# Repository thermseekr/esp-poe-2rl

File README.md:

# eumesmo-poe-2rl
PoE powered ESP32 based board featuring two SPST NO relays. Ideal for access control, doors, isolated zones or for installing anywhere you need to click dry contacts near some equipment or appliance.

## VERSION HISTORY

V1.6 - 2026/07/02 - Added CPU health LED.

V1.5 - 2026/06/13 - Repository renamed from ESP-POE-2RL to eumesmo-poe-2rl to align the design with the **eumesmo** line of building automation products.

V1.4 - 2026/06/10 - Terminal blocks replaced for 3.5mm pitch. Deleted temperature sensor, board decreased 8mm in length. LAN8710A rotated for shorter traces. Pull-up resistor for MDIO adjusted from 2.2k to 1.5k as suggested in the datasheet. Bulk and decoupling capacitor sizes and types adjusted for better performance.

V1.3 - 2025/06/29 - Layers reordered and board fully rerouted for better signal integrity.

V1.2 - 2024/12/07 - Connectors adjusted for best fitting the case.

V1.1 - 2024/11/29 - Initial release.

## LICENSE

This project is licensed under the [Creative Commons BY-NC 4.0 License](https://creativecommons.org/licenses/by-nc/4.0/).
Commercial use is not permitted without prior written consent. See the [LICENSE.txt](LICENSE.txt) file for details.

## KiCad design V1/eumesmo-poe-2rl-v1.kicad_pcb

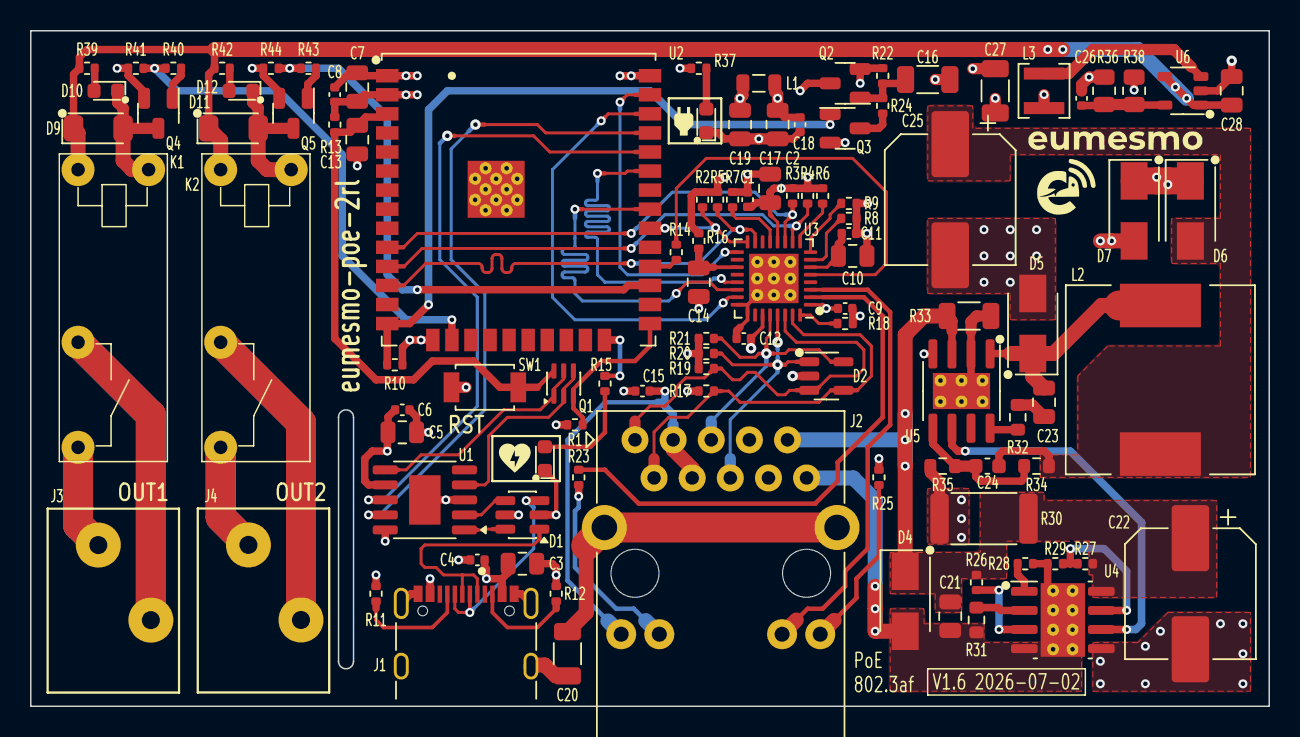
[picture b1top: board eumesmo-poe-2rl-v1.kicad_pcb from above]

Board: 4 copper layers, 82.5 x 45.0 mm, 105 parts (0 on the bottom side), 77 nets.

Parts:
C1, C4, C6, C8, C9, C12, C15, C18: 100nF/50V; C_0402_1005Metric
C2, C5, C7, C14, C17, C19, C28: 10uF/25V; C_0805_2012Metric
C3, C10, C13: 1uF/50V; C_0805_2012Metric
C11: 470pF/50V; C_0402_1005Metric
C16, C27: 22uF/10V; C_1206_3216Metric
C20: 1nF/2kV; C_1206_3216Metric
C21, C23: 100nF/100V; C_0805_2012Metric
C22: 22uF/100V; CP_Elec_8x10.5
C24: 12pF/50V; C_0603_1608Metric
C25: 470uF/16V; CP_Elec_8x10.5
C26: 22pF/50V; C_0402_1005Metric
D1: USBLC6-2SC6; SOT-23-6
D2: ESDS314DBV; SOT-23-5
D3: WHITE/0603; LED_0603_1608Metric
D4: SMAJ58A; D_SMA
D5: SS510; D_SMA
D6, D7: SS34; D_SMA
D8, D10, D12: WHITE; LED_0603_1608Metric
D9, D11: 1N4148; D_SOD-123
J1: USB_C_Receptacle_USB2.0; USB_C_Receptacle_GCT_USB4105-xx-A_16P_TopMnt_Horizontal
J2: RJ45 JACK; RJ45_HanRun_HY931147C
J3, J4: 250-202; TerminalBlock_Wago_250-202_1x02_P3.5mm_45Degree
K1, K2: G5NB-1A-E-DC5; Relay_SPST_Omron_G5NB-1A
L1: 2A/600R; L_0805_2012Metric
L2: 33uH/2,1A; L_12x12mm_H6mm
L3: 2,2uH/1,5A; L_3x3mm_H1.5mm
Q1: UMH3N; SOT-363_SC-70-6
Q2: WPM2015-3/TR; SOT-23
Q3: LMUN2211LT1G; SOT-23
Q4, Q5: MMBT2222A; SOT-23
R1, R10, R13, R16, R22, R29, R41, R44: 10k; R_0402_1005Metric
R2: 1.5k; R_0402_1005Metric
R3, R4, R5, R6, R7, R8, R9: 2.2k; R_0402_1005Metric
R11, R12: 5,1k; R_0402_1005Metric
R14: 33R; R_0402_1005Metric
R15, R37: 300R; R_0402_1005Metric
R17, R19, R20, R21: 49,9R; R_0402_1005Metric
R18: 12,1k; R_0402_1005Metric
R23, R25: 330R; R_0402_1005Metric
R24, R40, R43: 1k; R_0402_1005Metric
R26: 30,1k; R_0402_1005Metric
R27: 130k; R_0402_1005Metric
R28: 180k; R_0402_1005Metric
R30: 4,7k/1W; R_2512_6332Metric
R31: 4,42k/100mW; R_0603_1608Metric
R32: 5,1R/100mW; R_0603_1608Metric
R33: 30mR/250mW; R_1206_3216Metric
R34: 300k/100mW; R_0603_1608Metric
R35: 52,3k/100mW; R_0603_1608Metric
R36: 100k/0,125W; R_0805_2012Metric
R38: 22,1k/0,125W; R_0805_2012Metric
R39, R42: 680R; R_0402_1005Metric
SW1: RESET; SW_SPST_Xunpu_TS1088AR02016
U1: CH340K; SSOP-10-1EP_3.9x4.9mm_P1mm_EP2.1x3.3mm
U2: ESP32-WROOM-32UE-N16; ESP32-WROOM-32U
U3: LAN8710A; QFN-32-1EP_5x5mm_P0.5mm_EP3.3x3.3mm_ThermalVias
U4: TPS2376DDAR-H; SOIC-8-1EP_3.9x4.9mm_P1.27mm_EP2.95x4.9mm_Mask2.71x3.4mm_Th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
U5: TX4138; SOIC-8-1EP_3.9x4.9mm_P1.27mm_EP2.41x3.81mm_ThermalVias
U6: SY8089A1AAC; SOT-23-5_Shorter_Pins

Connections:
5VPOE: C24.1, C25.1, D6.2 (A), L2.2, R34.1
5VUSB: C3.1, C4.1, D1.5 (VBUS), D7.2 (A), J1.A4 (VBUS), J1.A9 (VBUS), J1.B4 (VBUS), J1.B9 (VBUS)
+3V3: C5.1, C6.1, C7.1, C8.1, C16.1, C26.1, C27.1, L3.2, Q2.2 (S), R1.1, R13.1, R22.1, R36.1, R37.1, U1.7 (VCC), U1.10 (V3), U2.2 (VDD)
+3V3A: C9.1, C12.1, C15.1, C19.1, J2.3 (CT), J2.4 (CT), J2.11 (LLED+), L1.2, R17.2, R19.2, R20.2, R21.2, U3.1 (VDD2A), U3.27 (VDD1A)
+3V3LAN: C1.1, C2.1, C17.1, C18.1, L1.1, Q2.3 (D), R2.1, R3.1, R4.1, R5.1, R6.1, R16.2, U3.12 (VDDIO)
+5V: C28.1, D6.1 (K), D7.1 (K), D9.1 (K), D11.1 (K), K1.1, K2.1, R39.1, R42.1, U6.1 (EN), U6.4 (IN)
/CPULED: D3.2 (A), R15.2
/CPUOK: R15.1, U2.24 (IO2)
/EMACCLK: R14.2, U3.5 (XTAL1/CLKIN)
/EMACMDC: U2.37 (IO23), U3.17 (MDC)
/EMACMDIO: R2.2, U2.30 (IO18), U3.16 (MDIO)
/EMACRX: R5.2, U2.12 (IO27), U3.15 (COL/CRS_DV/~MODE2)
/EMACRXCLK: R8.2, U3.7 (RXCLK/~PHYAD1)
/EMACRXD0: R3.2, U2.10 (IO25), U3.11 (RXD0/~MODE0)
/EMACRXD1: R4.2, U2.11 (IO26), U3.10 (RXD1/~MODE1)
/EMACRXD2: R6.2, U3.9 (RXD2/~RMIISEL)
/EMACRXD3: R9.2, U3.8 (RXD3/~PHYAD2)
/EMACRXD4: R7.2, U3.13 (RXER/RXD4/~PHYAD0)
/EMACTXD0: U2.31 (IO19), U3.22 (TXD0)
/EMACTXD1: U2.36 (IO22), U3.23 (TXD1)
/EMACTXEN: U2.33 (IO21), U3.21 (TXEN)
/ESPCLK: R14.1, U2.28 (IO17)
/ESPEN: C13.1, Q1.6 (C1), R13.2, SW1.2, U2.3 (EN)
/ESPPROG: Q1.3 (C2), R1.2, U2.25 (IO0)
/ETHLEDGA: J2.13 (RLED+), U3.3 (LED1/~REGOFF)
/ETHLEDGK: J2.14 (RLED-), R25.2
/ETHLEDY: R23.2, U3.2 (LED2/~INTSEL)
/ETHLEDYK: J2.12 (LLED-), R23.1
/ETHRXD+: D2.4 (I/03), J2.2 (RD+), R17.1, U3.31 (RXP)
/ETHRXD-: D2.3 (I/02), J2.1 (RD-), R19.1, U3.30 (RXN)
/ETHSH: C20.1, J2.15 (SHIELD)
/ETHTXD+: D2.1 (I/01), J2.6 (TD+), R20.1, U3.29 (TXP)
/ETHTXD-: D2.5 (I/04), J2.5 (TD-), R21.1, U3.28 (TXN)
/PHYNRST: C14.2, R16.1, U3.19 (~RST)
/PHYPWRBJT: Q3.3 (C), R24.2
/PHYPWRFET: C16.2, Q2.1 (G), R22.2, R24.1
/POWER/3V3LED: D8.2 (A), R37.2
/POWER/3V3REF: C26.2, R36.2, R38.1, U6.5 (FB)
/POWER/3V3SW: L3.1, U6.3 (LX)
/POWER/5VBS: C23.1, R32.1
/POWER/5VREF: C24.2, R34.2, R35.1, U5.5 (FB)
/POWER/5VSW: C23.2, D5.1 (K), L2.1, U5.1 (SW)
/POWER/BS: R32.2, U5.8 (BS)
/POWER/ILIM: R33.2, U5.2 (ILIM), U5.9 (ILIM)
/POWER/RCLASS: R31.1, U4.2 (CLASS)
/POWER/RDET: R26.2, U4.3 (DET)
/POWER/RILIM: R28.1, U4.1 (ILIM)
/POWER/VTAP: R27.2, R29.1, U4.7 (UVLO)
/RBIAS: R18.1, U3.32 (RBIAS)
/RELAY OUTPUTS/OUT1BJT: Q4.1 (B), R40.1
/RELAY OUTPUTS/OUT1CMD: D9.2 (A), D10.1 (K), K1.4, Q4.3 (C)
/RELAY OUTPUTS/OUT1LD: J3.1, K1.3
/RELAY OUTPUTS/OUT1LN: J3.2, K1.2
/RELAY OUTPUTS/OUT1ON: D10.2 (A), R39.2
/RELAY OUTPUTS/OUT2BJT: Q5.1 (B), R43.1
/RELAY OUTPUTS/OUT2CMD: D11.2 (A), D12.1 (K), K2.4, Q5.3 (C)
/RELAY OUTPUTS/OUT2LD: J4.1, K2.3
/RELAY OUTPUTS/OUT2LN: J4.2, K2.2
/RELAY OUTPUTS/OUT2ON: D12.2 (A), R42.2
/UARTNDTR: Q1.2 (B1), Q1.4 (E2), U1.4 (~DTR)
/UARTNRTS: Q1.1 (E1), Q1.5 (B2), U1.6 (~RTS)
/UARTRXD: U1.9 (RXD), U2.35 (TXD0/IO1)
/UARTTXD: U1.8 (TXD), U2.34 (RXD0/IO3)
/USBCC1: J1.A5 (CC1), R11.1
/USBCC2: J1.B5 (CC2), R12.1
/USBCD+: D1.1 (I/O1), J1.A6 (D+), J1.B6 (D+)
/USBCD-: D1.3 (I/O2), J1.A7 (D-), J1.B7 (D-)
/USBD+: D1.6 (I/O1), U1.1 (UD+)
/USBD-: D1.4 (I/O2), U1.2 (UD-)
/VDDCR: C10.1, C11.1, U3.6 (VDDCR)
GND: C1.2, C2.2, C3.2, C4.2, C5.2, C6.2, C7.2, C8.2, C9.2, C10.2, C11.2, C12.2, C13.2, C14.1, C15.2, C17.2, C18.2, C19.2, C20.2, C22.2, C25.2, C27.2, C28.2, D1.2 (GND), D2.2 (GND), D3.1 (K), D5.2 (A), D8.1 (K), J1.A1 (GND), J1.A12 (GND), J1.B1 (GND), J1.B12 (GND), J1.S1 (SHIELD), Q3.2 (E), Q4.2 (E), Q5.2 (E), R7.1, R8.1, R9.1, R10.1, R11.2, R12.2, R18.2, R25.1, R30.2, R35.2, R38.2, R41.2, R44.2, SW1.1, U1.3 (GND), U1.11 (GND), U2.1 (GND), U2.15 (GND), U2.38 (GND), U2.39 (GND), U3.24 (TXD2), U3.25 (TXD3), U3.33 (VSS), U4.5 (RTN), U5.4 (GND), U6.2 (GND)
OUT1: R40.2, R41.1, U2.16 (IO13)
OUT2: R43.2, R44.1, U2.27 (IO16)
PG: U4.6 (PG), U5.6 (EN)
PHYPWR: Q3.1 (B), R10.2, U2.14 (IO12)
POE+: C21.1, C22.1, D4.1 (K), J2.9 (V+), R26.1, R27.1, R30.1, R33.1, U4.8 (VDD), U5.3 (VIN)
POE-: C21.2, D4.2 (A), J2.10 (V-), R28.2, R29.2, R31.2, U4.4 (VSS), U4.9 (PPAD)

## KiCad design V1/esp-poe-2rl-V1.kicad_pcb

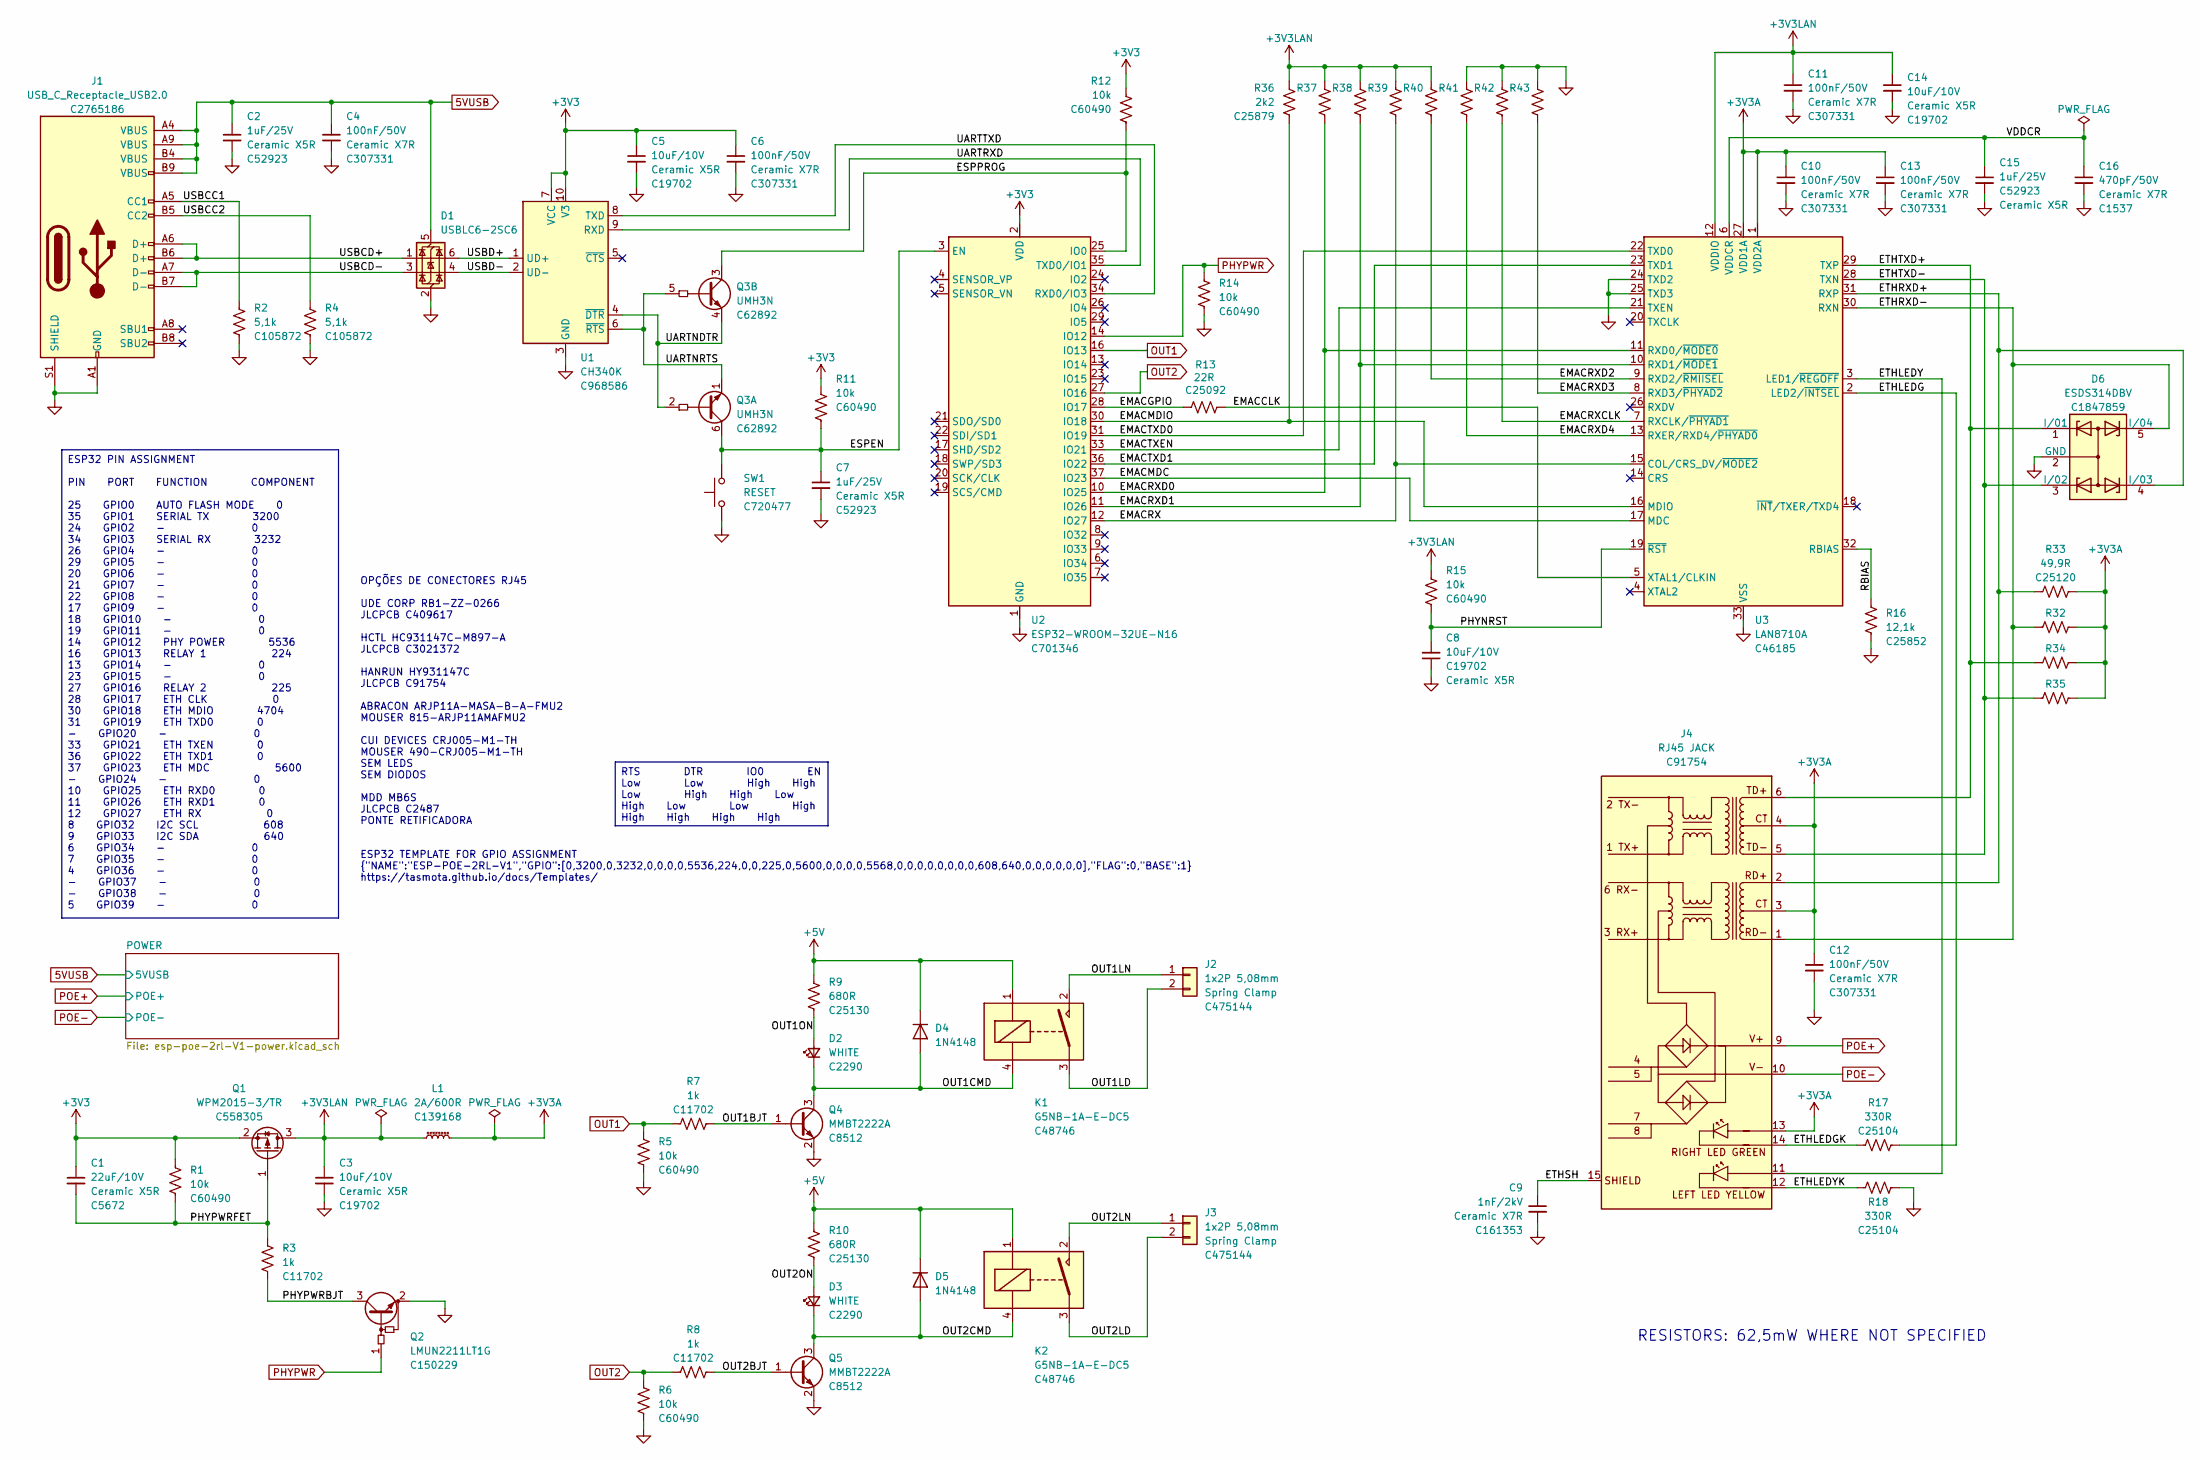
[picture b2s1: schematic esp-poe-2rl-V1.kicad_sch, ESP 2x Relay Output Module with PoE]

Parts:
C1: 22uF/10V; C_1206_3216Metric; Mfr PN CL31A226KPHNNNE; JLCPCB BOM 1
C2, C7, C15: 1uF/25V; C_0402_1005Metric; Mfr PN CL05A105KA5NQNC; JLCPCB BOM 1
C3, C8, C14: 10uF/10V; C_0603_1608Metric; Mfr PN CL10A106KP8NNNC; JLCPCB BOM 1
C4, C6, C10, C11, C12, C13: 100nF/50V; C_0402_1005Metric; Mfr PN CL05B104KB54PNC; JLCPCB BOM 1
C5: 10uF/10V; C_0603_1608Metric; Mfr PN CL10A106KP8NNNC; LCSC Part # C19702
C9: 1nF/2kV; C_1206_3216Metric; Mfr PN GR431BR7LA102KW66L; JLCPCB BOM 1
C16: 470pF/50V; C_0402_1005Metric; Mfr PN 0402B471K500NT; JLCPCB BOM 1
D1: USBLC6-2SC6; SOT-23-6; Mfr PN USBLC6-2SC6; JLCPCB BOM 1
D2, D3: WHITE; LED_0603_1608Metric; Mfr PN KT-0603W; LCSC Part # C2290
D4, D5: 1N4148; D_SOD-123; Mfr PN 1N4148W; JLCPCB BOM 1
D6: ESDS314DBV; SOT-23-5; Mfr PN ESDS314DBVR; JLCPCB BOM 1
J1: USB_C_Receptacle_USB2.0; USB_C_Receptacle_GCT_USB4105-xx-A_16P_TopMnt_Horizontal; Mfr PN TYPE-C 16PIN 2MD(073); JLCPCB BOM 1
J2, J3: 1x2P 5,08mm; TerminalBlock_Dibo_DB142R-5.08-2P_1x02_P5.08mm_Horizontal; Mfr PN KF142R-5.08-2P; JLCPCB BOM 1
J4: RJ45 JACK; RJ45_HanRun_HY931147C; Mfr PN HY931147C; JLCPCB BOM 1
K1, K2: G5NB-1A-E-DC5; Relay_SPST_Omron_G5NB-1A; Mfr PN G5NB-1A-E-DC5; JLCPCB BOM 1
L1: 2A/600R; L_0805_2012Metric; Mfr PN CBM201209U601T; JLCPCB BOM 1
Q1: WPM2015-3/TR; SOT-23; Mfr PN WPM2015-3/TR; JLCPCB BOM 1
Q2: LMUN2211LT1G; SOT-23; Mfr PN MMUN2211LT3G; LCSC Part # C150229
Q3: UMH3N; SOT-363_SC-70-6; Mfr PN UMH3N; JLCPCB BOM 1
Q4, Q5: MMBT2222A; SOT-23; Mfr PN MMBT2222A; JLCPCB BOM 1
R1, R5, R6, R11, R12, R14, R15: 10k; R_0402_1005Metric; Mfr PN RC0402FR-0710KL; LCSC Part # C60490
R2, R4: 5,1k; R_0402_1005Metric; Mfr PN RC0402FR-075K1L; JLCPCB BOM 1
R3, R7, R8: 1k; R_0402_1005Metric; Mfr PN 0402WGF1001TCE; LCSC Part # C11702
R9, R10: 680R; R_0402_1005Metric; Mfr PN 0402WGF6800TCE; LCSC Part # C25130
R13: 22R; R_0402_1005Metric; Mfr PN 0402WGF220JTCE; JLCPCB BOM 1
R16: 12,1k; R_0402_1005Metric; Mfr PN 0402WGF1212TCE; JLCPCB BOM 1
R17, R18: 330R; R_0402_1005Metric; Mfr PN 0402WGF3300TCE; LCSC Part # C25104
R32, R33, R34, R35: 49,9R; R_0402_1005Metric; Mfr PN 0402WGF499JTCE; JLCPCB BOM 1
R36, R37, R38, R39, R40, R41, R42, R43: 2k2; R_0402_1005Metric; Mfr PN 0402WGF2201TCE; LCSC Part # C25879
SW1: RESET; SW_SPST_Xunpu_TS1088AR02016; Mfr PN TS-1088-AR02016; JLCPCB BOM 1
U1: CH340K; SSOP-10-1EP_3.9x4.9mm_P1mm_EP2.1x3.3mm; Mfr PN CH340K; JLCPCB BOM 1
U2: ESP32-WROOM-32UE-N16; ESP32-WROOM-32U; Mfr PN ESP32-WROOM-32UE-N16; JLCPCB BOM 1
U3: LAN8710A; QFN-32-1EP_5x5mm_P0.5mm_EP3.3x3.3mm_ThermalVias; Mfr PN LAN8710A-EZC-TR; JLCPCB BOM 1

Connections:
5VUSB: C2.1, C4.1, D1.5 (VBUS), J1.A4 (VBUS), J1.A9 (VBUS), J1.B4 (VBUS), J1.B9 (VBUS); also elsewhere on the board
+3V3: C1.1, C5.1, C6.1, Q1.2 (S), R1.1, R11.1, R12.1, U1.7 (VCC), U1.10 (V3), U2.2 (VDD); also elsewhere on the board
+3V3A: C10.1, C12.1, C13.1, J4.3 (CT), J4.4 (CT), J4.13 (RLED+), L1.2, R32.2, R33.2, R34.2, R35.2, U3.1 (VDD2A), U3.27 (VDD1A)
+3V3LAN: C3.1, C11.1, C14.1, L1.1, Q1.3 (D), R15.2, R36.1, R37.1, R38.1, R39.1, R40.1, U3.12 (VDDIO)
+5V: D4.1 (K), D5.1 (K), K1.1, K2.1, R9.1, R10.1; also elsewhere on the board
/EMACCLK: R13.2, U3.5 (XTAL1/CLKIN)
/EMACGPIO: R13.1, U2.28 (IO17)
/EMACMDC: U2.37 (IO23), U3.17 (MDC)
/EMACMDIO: R36.2, U2.30 (IO18), U3.16 (MDIO)
/EMACRX: R39.2, U2.12 (IO27), U3.15 (COL/CRS_DV/~MODE2)
/EMACRXCLK: R42.2, U3.7 (RXCLK/~PHYAD1)
/EMACRXD0: R37.2, U2.10 (IO25), U3.11 (RXD0/~MODE0)
/EMACRXD1: R38.2, U2.11 (IO26), U3.10 (RXD1/~MODE1)
/EMACRXD2: R40.2, U3.9 (RXD2/~RMIISEL)
/EMACRXD3: R43.2, U3.8 (RXD3/~PHYAD2)
/EMACRXD4: R41.2, U3.13 (RXER/RXD4/~PHYAD0)
/EMACTXD0: U2.31 (IO19), U3.22 (TXD0)
/EMACTXD1: U2.36 (IO22), U3.23 (TXD1)
/EMACTXEN: U2.33 (IO21), U3.21 (TXEN)
/ESPEN: C7.1, Q3.6 (C1), R11.2, SW1.2, U2.3 (EN)
/ESPPROG: Q3.3 (C2), R12.2, U2.25 (IO0)
/ETHLEDG: R17.2, U3.2 (LED2/~INTSEL)
/ETHLEDGK: J4.14 (RLED-), R17.1
/ETHLEDY: J4.11 (LLED+), U3.3 (LED1/~REGOFF)
/ETHLEDYK: J4.12 (LLED-), R18.1
/ETHRXD+: D6.4 (I/03), J4.2 (RD+), R33.1, U3.31 (RXP)
/ETHRXD-: D6.5 (I/04), J4.1 (RD-), R32.1, U3.30 (RXN)
/ETHSH: C9.1, J4.15 (SHIELD)
/ETHTXD+: D6.1 (I/01), J4.6 (TD+), R34.1, U3.29 (TXP)
/ETHTXD-: D6.3 (I/02), J4.5 (TD-), R35.1, U3.28 (TXN)
/OUT1BJT: Q4.1 (B), R7.1
/OUT1CMD: D2.1 (K), D4.2 (A), K1.4, Q4.3 (C)
/OUT1LD: J2.2, K1.3
/OUT1LN: J2.1, K1.2
/OUT1ON: D2.2 (A), R9.2
/OUT2BJT: Q5.1 (B), R8.1
/OUT2CMD: D3.1 (K), D5.2 (A), K2.4, Q5.3 (C)
/OUT2LD: J3.2, K2.3
/OUT2LN: J3.1, K2.2
/OUT2ON: D3.2 (A), R10.2
/PHYNRST: C8.2, R15.1, U3.19 (~RST)
/PHYPWRBJT: Q2.3 (C), R3.2
/PHYPWRFET: C1.2, Q1.1 (G), R1.2, R3.1
/RBIAS: R16.1, U3.32 (RBIAS)
/UARTNDTR: Q3.2 (B1), Q3.4 (E2), U1.4 (~DTR)
/UARTNRTS: Q3.1 (E1), Q3.5 (B2), U1.6 (~RTS)
/UARTRXD: U1.9 (RXD), U2.35 (TXD0/IO1)
/UARTTXD: U1.8 (TXD), U2.34 (RXD0/IO3)
/USBCC1: J1.A5 (CC1), R2.1
/USBCC2: J1.B5 (CC2), R4.1
/USBCD+: D1.1 (I/O1), J1.A6 (D+), J1.B6 (D+)
/USBCD-: D1.3 (I/O2), J1.A7 (D-), J1.B7 (D-)
/USBD+: D1.6 (I/O1), U1.1 (UD+)
/USBD-: D1.4 (I/O2), U1.2 (UD-)
/VDDCR: C15.1, C16.1, U3.6 (VDDCR)
GND: C2.2, C3.2, C4.2, C5.2, C6.2, C7.2, C8.1, C9.2, C10.2, C11.2, C12.2, C13.2, C14.2, C15.2, C16.2, D1.2 (GND), D6.2 (GND), J1.A1 (GND), J1.A12 (GND), J1.B1 (GND), J1.B12 (GND), J1.S1 (SHIELD), Q2.2 (E), Q4.2 (E), Q5.2 (E), R2.2, R4.2, R5.2, R6.2, R14.1, R16.2, R18.2, R41.1, R42.1, R43.1, SW1.1, U1.3 (GND), U1.11 (GND), U2.1 (GND), U2.15 (GND), U2.38 (GND), U2.39 (GND), U3.24 (TXD2), U3.25 (TXD3), U3.33 (VSS); also elsewhere on the board
OUT1: R5.1, R7.2, U2.16 (IO13)
OUT2: R6.1, R8.2, U2.27 (IO16)
PHYPWR: Q2.1 (B), R14.2, U2.14 (IO12)
POE+: J4.9 (V+); also elsewhere on the board
POE-: J4.10 (V-); also elsewhere on the board

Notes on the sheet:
OPÇÕES DE CONECTORES RJ45 UDE CORP RB1-ZZ-0266 JLCPCB C409617 HCTL HC931147C-M897-A JLCPCB C3021372 HANRUN HY931147C JLCPCB C91754 ABRACON ARJP11A-MASA-B-A-FMU2 MOUSER 815-ARJP11AMAFMU2 CUI DEVICES CRJ005-M1-TH MOUSER 490-CRJ005-M1-TH SEM LEDS SEM DIODOS MDD MB6S JLCPCB C2487 PONTE RETIFICADORA
ESP32 TEMPLATE FOR GPIO ASSIGNMENT {"NAME":"ESP-POE-2RL-V1","GPIO":[0,3200,0,3232,0,0,0,0,5536,224,0,0,225,0,5600,0,0,0,0,5568,0,0,0,0,0,0,0,0,608,640,0,0,0,0,0,0],"FLAG":0,"BASE":1} https://tasmota.github.io/docs/Templates/
RESISTORS: 62,5mW WHERE NOT SPECIFIED
ESP32 PIN ASSIGNMENT PIN PORT FUNCTION COMPONENT 25 GPIO0 AUTO FLASH MODE 0 35 GPIO1 SERIAL TX 3200 24 GPIO2 - 0 34 GPIO3 SERIAL RX 3232 26 GPIO4 - 0 29 GPIO5 - 0 20 GPIO6 - 0 21 GPIO7 - 0 22 GPIO8 - 0 17 GPIO9 - 0 18 GPIO10 - 0 19 GPIO11 - 0 14 GPIO12 PHY POWER 5536 16 GPIO13 RELAY 1 224 13 GPIO14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
RTS DTR IO0 EN Low Low High High Low High High Low High Low Low High High High High High

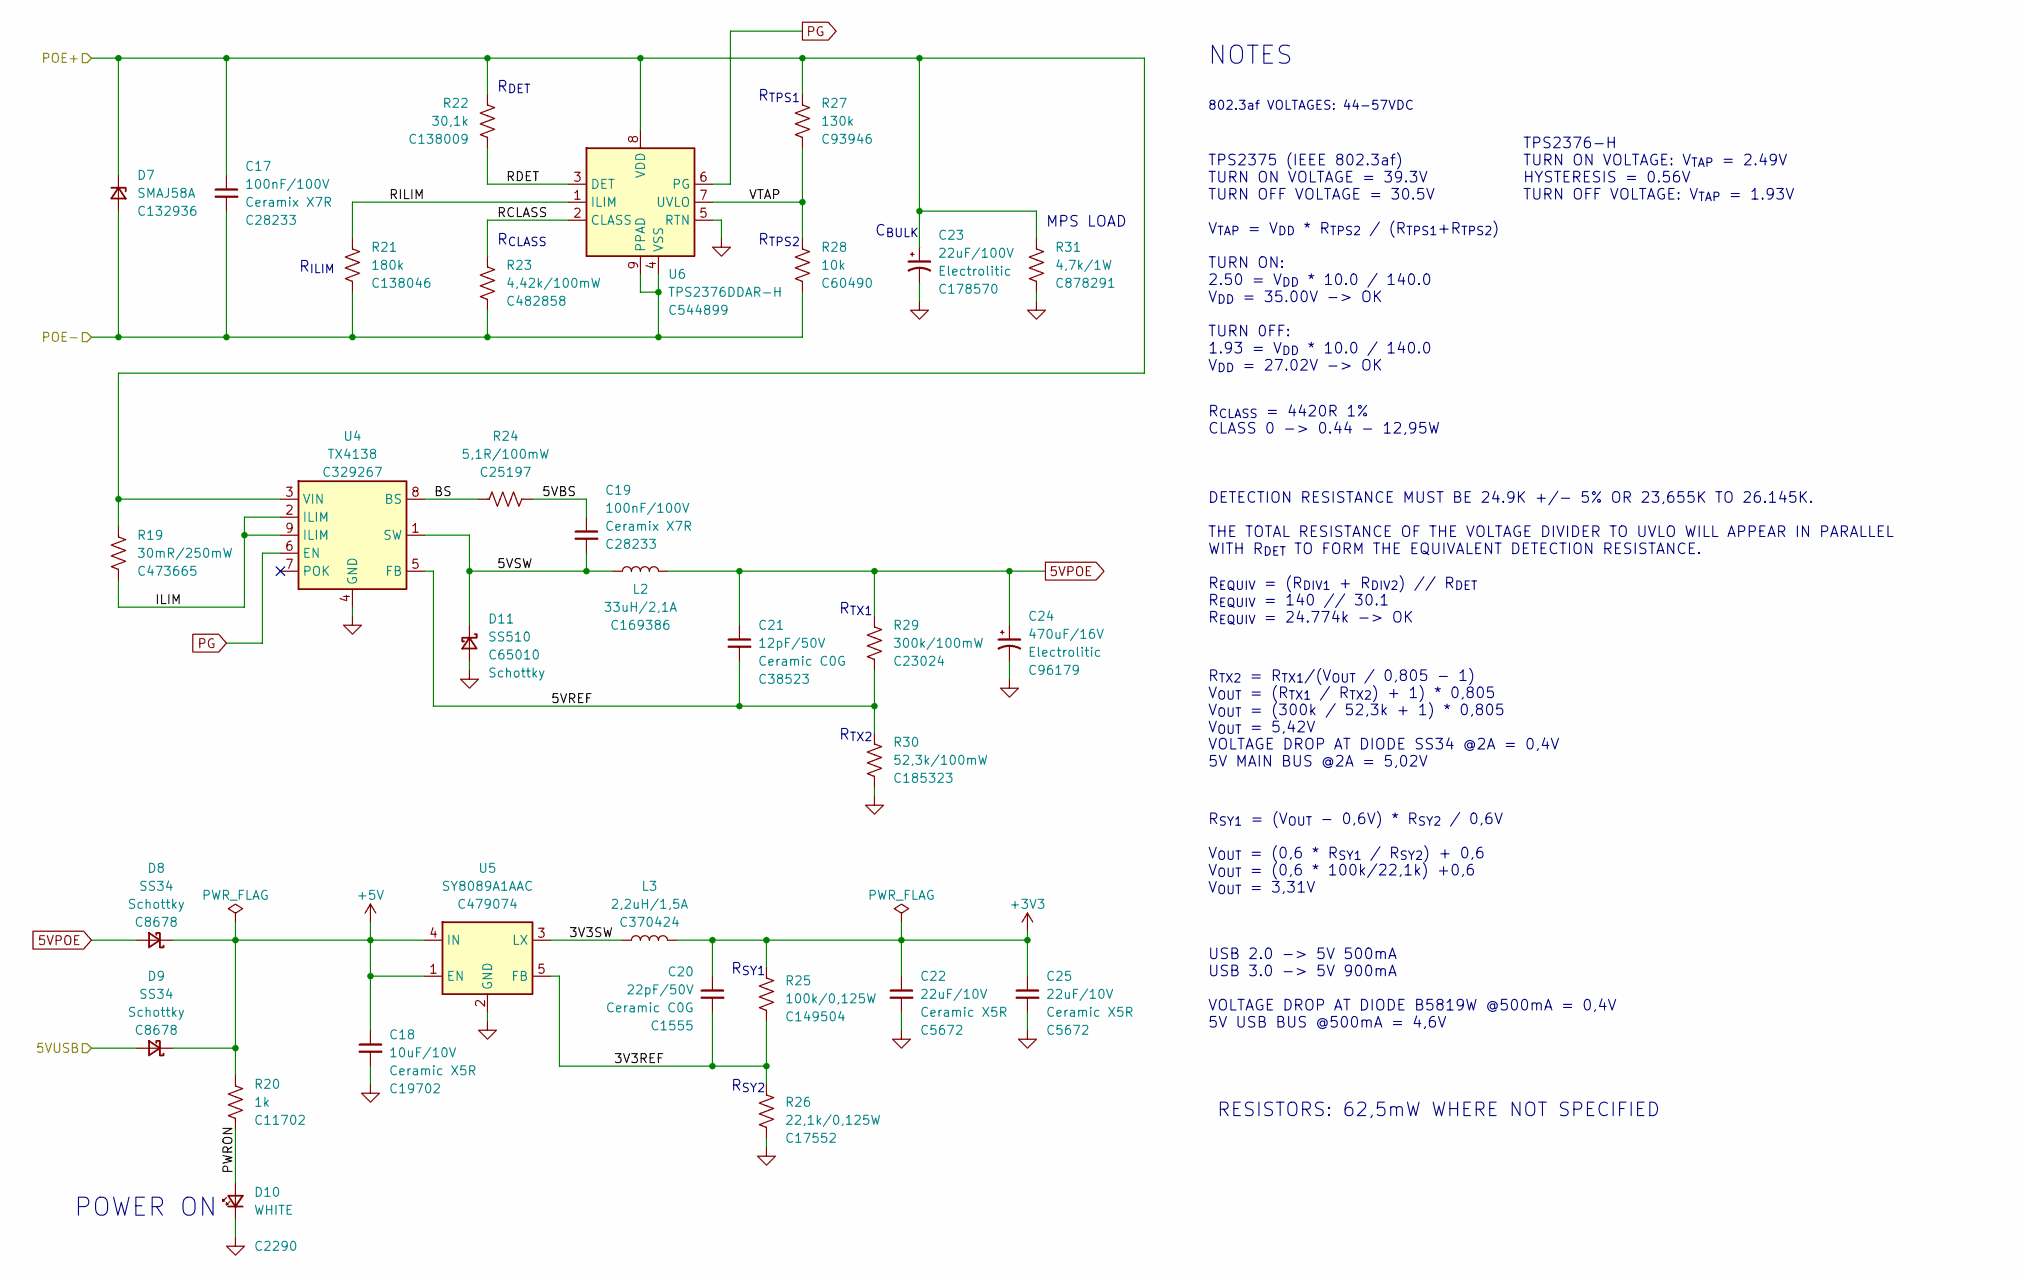
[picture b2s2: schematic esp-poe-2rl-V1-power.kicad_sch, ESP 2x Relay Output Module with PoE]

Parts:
C17: 100nF/100V; C_0805_2012Metric; Mfr PN CL21B104KCFNNNE; JLCPCB BOM 1
C18: 10uF/10V; C_0603_1608Metric; Mfr PN CL10A106KP8NNNC; JLCPCB BOM 1
C19: 100nF/100V; C_0805_2012Metric; Mfr PN CL21B104KCFNNNE; LCSC Part # C28233
C20: 22pF/50V; C_0402_1005Metric; Mfr PN 0402CG220J500NT; JLCPCB BOM 1
C21: 12pF/50V; C_0603_1608Metric; Mfr PN CL10C120JB8NNNC; JLCPCB BOM 1
C22, C25: 22uF/10V; C_1206_3216Metric; Mfr PN CL31A226KPHNNNE; JLCPCB BOM 1
C23: 22uF/100V; CP_Elec_8x10.5; Mfr PN EEEFK2A220P; LCSC Part # C178570
C24: 470uF/16V; CP_Elec_8x10.5; Mfr PN CS1C471M-CRF10; JLCPCB BOM 1
D7: SMAJ58A; D_SMA; Mfr PN SMAJ58A-TR; JLCPCB BOM 1
D8, D9: SS34; D_SMA; Mfr PN SS34; JLCPCB BOM 1
D10: WHITE; LED_0603_1608Metric; Mfr PN KT-0603W; LCSC Part # C2290
D11: SS510; D_SMA; Mfr PN SS510; JLCPCB BOM 1
L2: 33uH/2,1A; L_12x12mm_h6mm; Mfr PN SWRB1205S-330MT; JLCPCB BOM 1
L3: 2,2uH/1,5A; L_3x3mm_h1.5mm; Mfr PN SPH3015H2R2MT; JLCPCB BOM 1
R19: 30mR/250mW; R_1206_3216Metric; Mfr PN 1206W3F300MT5E; LCSC Part # C473665
R20: 1k; R_0402_1005Metric; Mfr PN 0402WGF1001TCE; LCSC Part # C11702
R21: 180k; R_0402_1005Metric; Mfr PN RC0402FR-07180KL; JLCPCB BOM 1
R22: 30,1k; R_0402_1005Metric; Mfr PN RC0402FR-0730K1L; JLCPCB BOM 1
R23: 4,42k/100mW; R_0603_1608Metric; Mfr PN RC0603FR-074K42L; JLCPCB BOM 1
R24: 5,1R/100mW; R_0603_1608Metric; Mfr PN 0603WAF510KT5E; LCSC Part # C25197
R25: 100k/0,125W; R_0805_2012Metric; Mfr PN 0805W8F1003T5E; JLCPCB BOM 1
R26: 22,1k/0,125W; R_0805_2012Metric; Mfr PN 0805W8F2212T5E; JLCPCB BOM 1
R27: 130k; R_0402_1005Metric; Mfr PN RC0402FR-07130KL; JLCPCB BOM 1
R28: 10k; R_0402_1005Metric; Mfr PN RC0402FR-0710KL; JLCPCB BOM 1
R29: 300k/100mW; R_0603_1608Metric; Mfr PN 0603WAF3003T5E; JLCPCB BOM 1
R30: 52,3k/100mW; R_0603_1608Metric; Mfr PN RC0603FR-0752K3L; JLCPCB BOM 1
R31: 4,7k/1W; R_2512_6332Metric; Mfr PN RC2512JK-074K7L; JLCPCB BOM 1
U4: TX4138; SOIC-8-1EP_3.9x4.9mm_P1.27mm_EP2.41x3.81mm_ThermalVias; Mfr PN TX4138; JLCPCB BOM 1
U5: SY8089A1AAC; SOT-23-5_Shorter_Pins; Mfr PN SY8089A1AAC; JLCPCB BOM 1
U6: TPS2376DDAR-H; SOIC-8-1EP_3.9x4.9mm_P1.27mm_EP2.95x4.9mm_Mask2.71x3.4mm_Th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; Mfr PN TPS2376DDAR-H; JLCPCB BOM 1

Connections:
5VPOE: C21.1, C24.1, D8.2 (A), L2.2, R29.1
5VUSB: D9.2 (A); also elsewhere on the board
+3V3: C20.1, C22.1, C25.1, L3.2, R25.1; also elsewhere on the board
+5V: C18.1, D8.1 (K), D9.1 (K), R20.1, U5.1 (EN), U5.4 (IN); also elsewhere on the board
/POWER/3V3REF: C20.2, R25.2, R26.1, U5.5 (FB)
/POWER/3V3SW: L3.1, U5.3 (LX)
/POWER/5VBS: C19.1, R24.1
/POWER/5VREF: C21.2, R29.2, R30.1, U4.5 (FB)
/POWER/5VSW: C19.2, D11.1 (K), L2.1, U4.1 (SW)
/POWER/BS: R24.2, U4.8 (BS)
/POWER/ILIM: R19.2, U4.2 (ILIM), U4.9 (ILIM)
/POWER/PWRON: D10.2 (A), R20.2
/POWER/RCLASS: R23.1, U6.2 (CLASS)
/POWER/RDET: R22.2, U6.3 (DET)
/POWER/RILIM: R21.1, U6.1 (ILIM)
/POWER/VTAP: R27.2, R28.1, U6.7 (UVLO)
GND: C18.2, C22.2, C23.2, C24.2, C25.2, D10.1 (K), D11.2 (A), R26.2, R30.2, R31.2, U4.4 (GND), U5.2 (GND), U6.5 (RTN); also elsewhere on the board
PG: U4.6 (EN), U6.6 (PG)
POE+: C17.1, C23.1, D7.1 (K), R19.1, R22.1, R27.1, R31.1, U4.3 (VIN), U6.8 (VDD); also elsewhere on the board
POE-: C17.2, D7.2 (A), R21.2, R23.2, R28.2, U6.4 (VSS), U6.9 (PPAD); also elsewhere on the board

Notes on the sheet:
R_{TPS1}
R_{TX2}
DETECTION RESISTANCE MUST BE 24.9K +/- 5% OR 23,655K TO 26.145K. THE TOTAL RESISTANCE OF THE VOLTAGE DIVIDER TO UVLO WILL APPEAR IN PARALLEL WITH R_{DET} TO FORM THE EQUIVALENT DETECTION RESISTANCE. R_{EQUIV} = (R_{DIV1} + R_{DIV2}) // R_{DET} R_{EQUIV} = 140 // 30.1 R_{EQUIV} = 24.774k -> OK
R_{SY2}
RESISTORS: 62,5mW WHERE NOT SPECIFIED
POWER ON
R_{CLASS} = 4420R 1% CLASS 0 -> 0.44 - 12,95W
R_{SY1}
R_{CLASS}
R_{TX2} = R_{TX1}/(V_{OUT} / 0,805 - 1) V_{OUT} = (R_{TX1} / R_{TX2}) + 1) * 0,805 V_{OUT} = (300k / 52,3k + 1) * 0,805 V_{OUT} = 5,42V VOLTAGE DROP AT DIODE SS34 @2A = 0,4V 5V MAIN BUS @2A = 5,02V
C_{BULK}
R_{ILIM}
USB 2.0 -> 5V 500mA USB 3.0 -> 5V 900mA VOLTAGE DROP AT DIODE B5819W @500mA = 0,4V 5V USB BUS @500mA = 4,6V
TPS2375 (IEEE 802.3af) TURN ON VOLTAGE = 39.3V TURN OFF VOLTAGE = 30.5V
TPS2376-H TURN ON VOLTAGE: V_{TAP} = 2.49V HYSTERESIS = 0.56V TURN OFF VOLTAGE: V_{TAP} = 1.93V
R_{SY1} = (V_{OUT} - 0,6V) * R_{SY2} / 0,6V V_{OUT} = (0,6 * R_{SY1} / R_{SY2}) + 0,6 V_{OUT} = (0,6 * 100k/22,1k) +0,6 V_{OUT} = 3,31V
R_{TPS2}
R_{TX1}
NOTES
MPS LOAD
R_{DET}
802.3af VOLTAGES: 44-57VDC
V_{TAP} = V_{DD} * R_{TPS2} / (R_{TPS1}+R_{TPS2}) TURN ON: 2.50 = V_{DD} * 10.0 / 140.0 V_{DD} = 35.00V -> OK TURN 0FF: 1.93 = V_{DD} * 10.0 / 140.0 V_{DD} = 27.02V -> OK

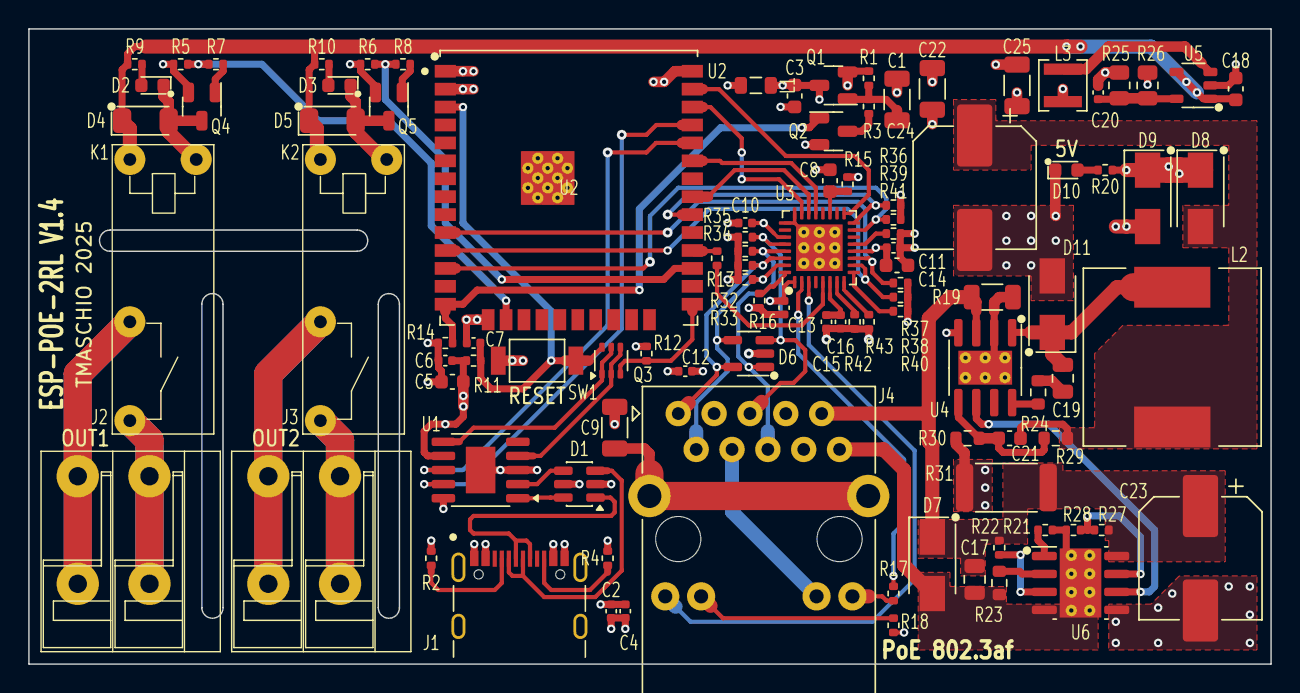
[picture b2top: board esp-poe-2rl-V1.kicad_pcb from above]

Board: 4 copper layers, 88.0 x 45.0 mm, 100 parts (0 on the bottom side), 75 nets.

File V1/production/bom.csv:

Designator,Footprint,Quantity,Value,LCSC Part #
"C1, C22, C25",1206,3,22uF/10V,C5672
"C10, C11, C12, C13, C4, C6",0402,6,100nF/50V,C307331
"C14, C18, C3, C5, C8",0603,5,10uF/10V,C19702
"C15, C2, C7",0402,3,1uF/25V,C52923
C16,0402,1,470pF/50V,C1537
"C17, C19",0805,2,100nF/100V,C28233
C20,0402,1,22pF/50V,C1555
C21,0603,1,12pF/50V,C38523
C23,CP_Elec_8x10.5,1,22uF/100V,C178570
C24,CP_Elec_8x10.5,1,470uF/16V,C96179
C9,1206,1,1nF/2kV,C161353
D1,SOT-23-6,1,USBLC6-2SC6,C7519
"D10, D2, D3",0603,3,WHITE,C2290
D11,D_SMA,1,SS510,C65010
"D4, D5",D_SOD-123,2,1N4148,C81598
D6,SOT-23-5,1,ESDS314DBV,C1847859
D7,D_SMA,1,SMAJ58A,C132936
"D8, D9",D_SMA,2,SS34,C8678
J1,USB_C_Receptacle_GCT_USB4105-xx-A_16P_TopMnt_Horizontal,1,USB_C_Receptacle_USB2.0,C2765186
"J2, J3",TerminalBlock_Dibo_DB142R-5.08-2P_1x02_P5.08mm_Horizontal,2,"1x2P 5,08mm",C475144
J4,RJ45_HanRun_HY931147C,1,RJ45 JACK,C91754
"K1, K2",Relay_SPST_Omron_G5NB-1A,2,G5NB-1A-E-DC5,C48746
L1,0805,1,2A/600R,C139168
L2,L_12x12mm_h6mm,1,"33uH/2,1A",C169386
L3,L_3x3mm_h1.5mm,1,"2,2uH/1,5A",C370424
Q1,SOT-23,1,WPM2015-3/TR,C558305
Q2,SOT-23,1,LMUN2211LT1G,C150229
Q3,SOT-363_SC-70-6,1,UMH3N,C62892
"Q4, Q5",SOT-23,2,MMBT2222A,C8512
"R1, R11, R12, R14, R15, R28, R5, R6",0402,8,10k,C60490
"R10, R9",0402,2,680R,C25130
R13,0402,1,22R,C25092
R16,0402,1,"12,1k",C25852
"R17, R18",0402,2,330R,C25104
R19,1206,1,30mR/250mW,C473665
"R2, R4",0402,2,"5,1k",C105872
"R20, R3, R7, R8",0402,4,1k,C11702
R21,0402,1,180k,C138046
R22,0402,1,"30,1k",C138009
R23,0603,1,"4,42k/100mW",C482858
R24,0603,1,"5,1R/100mW",C25197
R25,0805,1,"100k/0,125W",C149504
R26,0805,1,"22,1k/0,125W",C17552
R27,0402,1,130k,C93946
R29,0603,1,300k/100mW,C23024
R30,0603,1,"52,3k/100mW",C185323
R31,2512,1,"4,7k/1W",C878291
"R32, R33, R34, R35",0402,4,"49,9R",C25120
"R36, R37, R38, R39, R40, R41, R42, R43",0402,8,2k2,C25879
SW1,SW_SPST_Xunpu_TS1088AR02016,1,RESET,C720477
U1,SSOP-10-1EP_3.9x4.9mm_P1mm_EP2.1x3.3mm,1,CH340K,C968586
U2,ESP32-WROOM-32U,1,ESP32-WROOM-32UE-N16,C701346
U3,QFN-32-1EP_5x5mm_P0.5mm_EP3.3x3.3mm_ThermalVias,1,LAN8710A,C46185
U4,SOIC-8-1EP_3.9x4.9mm_P1.27mm_EP2.41x3.81mm_ThermalVias,1,TX4138,C329267
U5,SOT-23-5_Shorter_Pins,1,SY8089A1AAC,C479074
U6,SOIC-8-1EP_3.9x4.9mm_P1.27mm_EP2.95x4.9mm_Mask2.71x3.4mm_ThermalVias,1,TPS2376DDAR-H,C544899
